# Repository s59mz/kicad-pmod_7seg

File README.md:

# kicad-pmod_7seg
PMOD PCB module for 7-Segment Display 

Schematic:
[kicad-pmod_7seg.pdf](kicad-pmod_7seg.pdf)

BOM:
[kicad-pmod_7seg.csv](kicad-pmod_7seg.csv)

Gerbers:
[gerbers.zip](https://github.com/s59mz/kicad-pmod_7seg/raw/main/gerbers.zip)

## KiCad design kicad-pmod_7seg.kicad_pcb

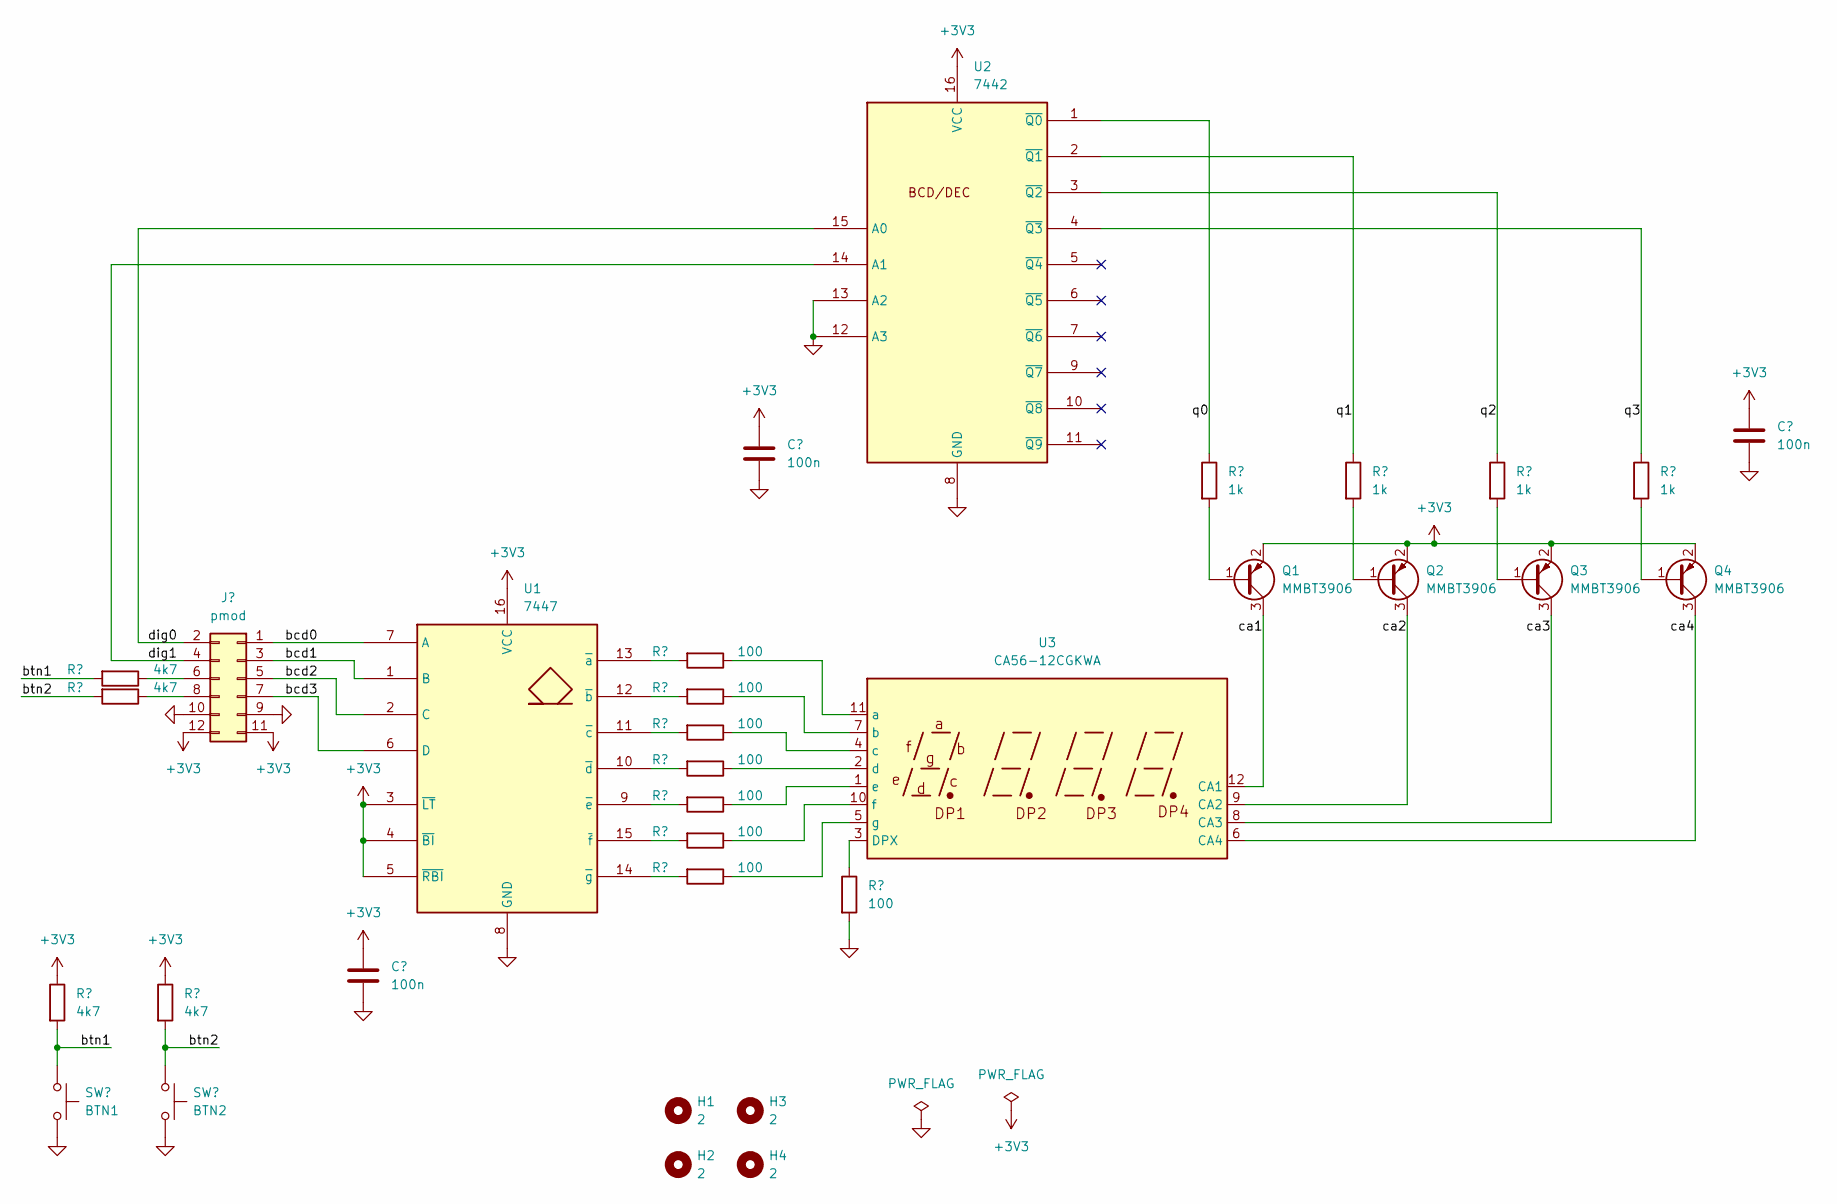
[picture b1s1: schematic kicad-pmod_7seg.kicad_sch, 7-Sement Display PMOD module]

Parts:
C1, C2, C3: 100n; C_0603_1608Metric_Pad1.08x0.95mm_HandSolder
H1, H2, H3, H4: 2; MountingHole_2.2mm_M2
J1: pmod; PinHeader_2x06_P2.54mm_Horizontal
Q1, Q2, Q3, Q4: MMBT3906; SOT-23
R1, R2, R3, R4: 4k7; R_0603_1608Metric_Pad0.98x0.95mm_HandSolder
R5, R6, R7, R8, R9, R10, R11, R16: 100; R_0603_1608Metric_Pad0.98x0.95mm_HandSolder
R12, R13, R14, R15: 1k; R_0603_1608Metric_Pad0.98x0.95mm_HandSolder
SW1: BTN1; SW_PUSH_6mm
SW2: BTN2; SW_PUSH_6mm
U1: 7447; DIP-16_W7.62mm_LongPads
U2: 7442; DIP-16_W7.62mm_LongPads
U3: CA56-12CGKWA

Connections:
+3V3: C1.1, C2.1, C3.1, J1.11, J1.12, Q1.2 (E), Q2.2 (E), Q3.2 (E), Q4.2 (E), R1.1, R4.1, U1.3 (~LT), U1.4 (~BI), U1.5 (~RBI), U1.16 (VCC), U2.16 (VCC)
/bcd0: J1.1, U1.7 (A)
/bcd1: J1.3, U1.1 (B)
/bcd2: J1.5, U1.2 (C)
/bcd3: J1.7, U1.6 (D)
/btn1: R1.2, R2.2, SW1.1
/btn2: R3.2, R4.2, SW2.1
/ca1: Q1.3 (C), U3.12 (CA1)
/ca2: Q2.3 (C), U3.9 (CA2)
/ca3: Q3.3 (C), U3.8 (CA3)
/ca4: Q4.3 (C), U3.6 (CA4)
/dig0: J1.2, U2.15 (A0)
/dig1: J1.4, U2.14 (A1)
/q0: R12.1, U2.1 (~Q0)
/q1: R13.1, U2.2 (~Q1)
/q2: R14.1, U2.3 (~Q2)
/q3: R15.1, U2.4 (~Q3)
GND: C1.2, C2.2, C3.2, J1.9, J1.10, R16.2, SW1.2, SW2.2, U1.8 (GND), U2.8 (GND), U2.12 (A3), U2.13 (A2)
unnamed: J1.6, R2.1
unnamed: J1.8, R3.1
unnamed: Q1.1 (B), R12.2
unnamed: Q2.1 (B), R13.2
unnamed: Q3.1 (B), R14.2
unnamed: Q4.1 (B), R15.2
unnamed: R5.2, U1.13 (~a)
unnamed: R6.2, U1.12 (~b)
unnamed: R7.2, U1.11 (~c)
unnamed: R8.2, U1.10 (~d)
unnamed: R9.2, U1.9 (~e)
unnamed: R10.2, U1.15 (~f)
unnamed: R11.2, U1.14 (~g)
unnamed: R16.1, U3.3 (DPX)
unnamed: R5.1, U3.11 (a)
unnamed: R6.1, U3.7 (b)
unnamed: R7.1, U3.4 (c)
unnamed: R8.1, U3.2 (d)
unnamed: R9.1, U3.1 (e)
unnamed: R10.1, U3.10 (f)
unnamed: R11.1, U3.5 (g)

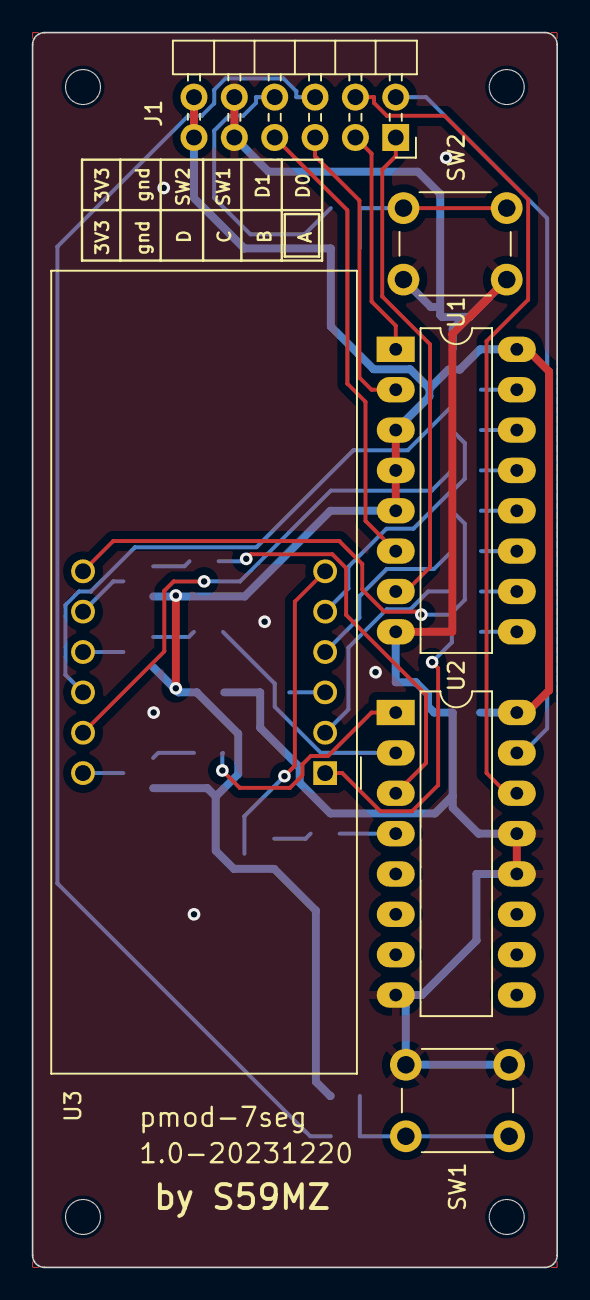
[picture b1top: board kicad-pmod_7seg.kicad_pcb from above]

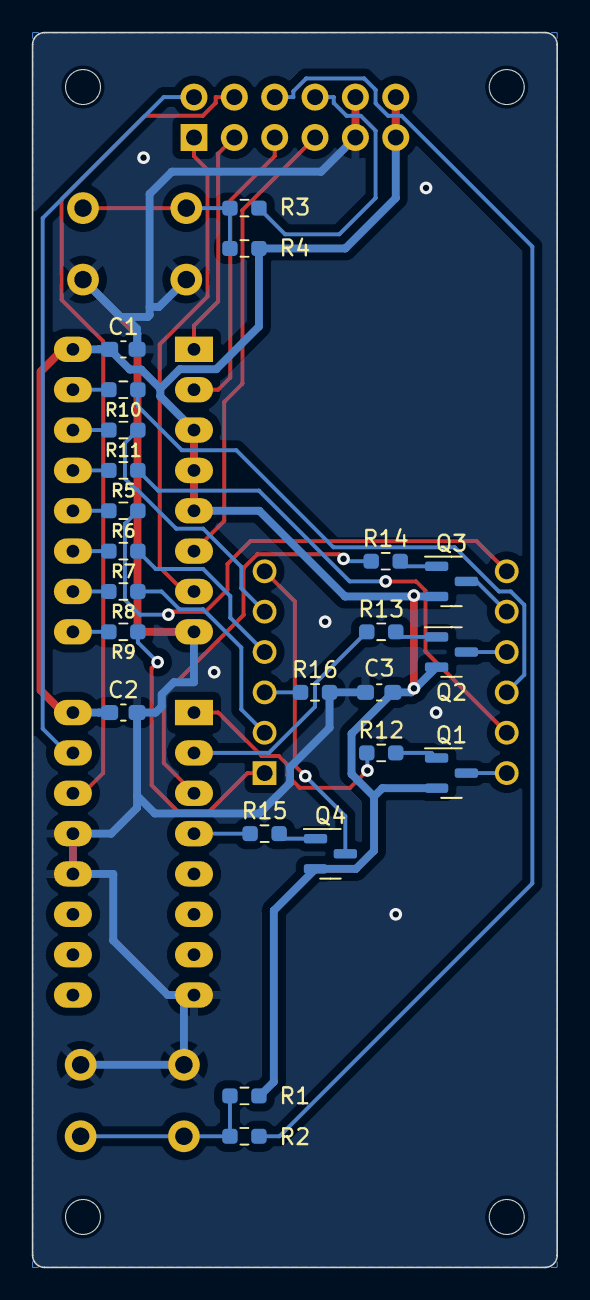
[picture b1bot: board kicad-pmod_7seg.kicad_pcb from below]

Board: 2 copper layers, 33.0 x 77.7 mm, 33 parts (23 on the bottom side), 39 nets.

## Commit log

2024-01-01 updated resistoor values
